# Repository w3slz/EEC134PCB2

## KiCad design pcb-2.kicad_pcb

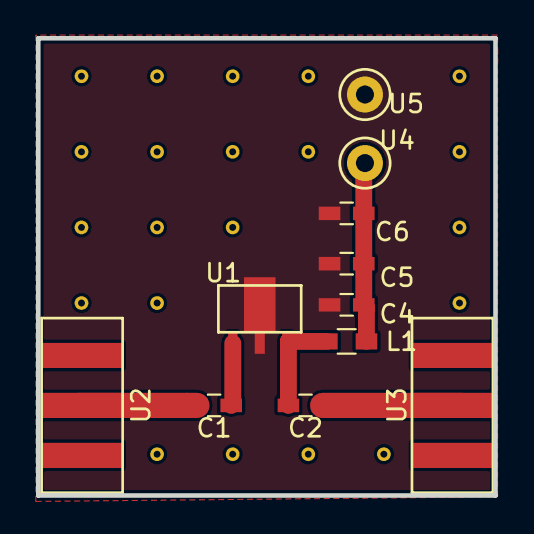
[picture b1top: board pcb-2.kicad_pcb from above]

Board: 2 copper layers, 25.4 x 25.4 mm, 11 parts (0 on the bottom side), 6 nets.

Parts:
C1, C2: 100n; C_0603_HandSoldering
C4: 68p; C_0603_HandSoldering
C5: 1.2n; C_0603_HandSoldering
C6: 1u; C_0603_HandSoldering
L1: 43n; L_0603_HandSoldering
U1: ADL5611
U2, U3: SMA
U4: VCC; Test_Point_Keystone_5000-5004_Miniature
U5: GND; Test_Point_Keystone_5000-5004_Miniature

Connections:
GND: C4.1, C5.1, C6.1, U1.2, U5.1
unnamed: C1.1, U1.1
unnamed: C1.2, U2.2
unnamed: C2.1, U3.2
unnamed: C2.2, L1.2, U1.3
unnamed: C4.2, C5.2, C6.2, L1.1, U4.1
